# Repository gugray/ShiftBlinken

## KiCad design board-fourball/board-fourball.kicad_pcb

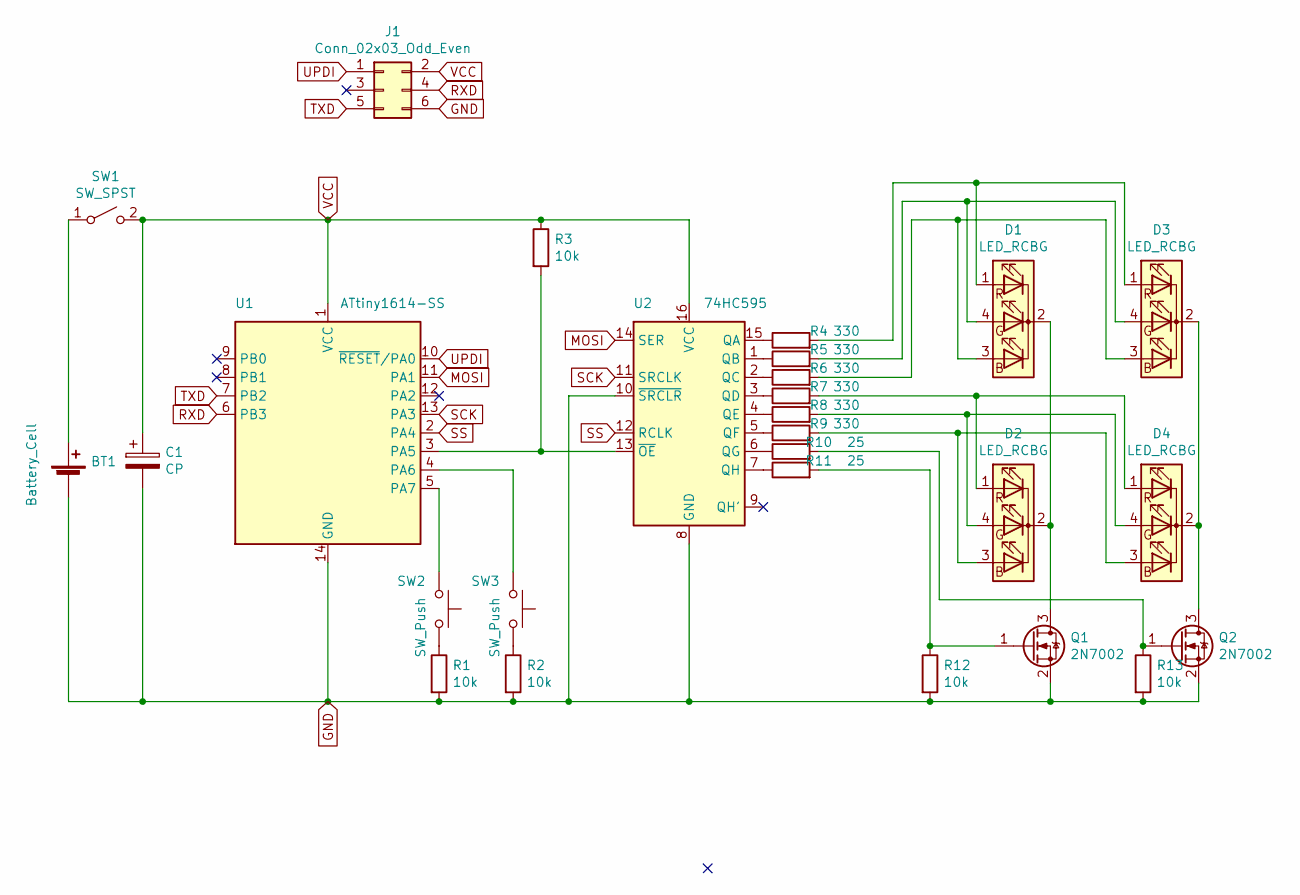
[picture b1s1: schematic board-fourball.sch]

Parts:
BT1: Battery_Cell; BatteryHolder_Keystone_3002_1x2032
C1: CP; CP_Radial_D5.0mm_P2.00mm
D1, D2, D3, D4: LED_RCBG; LED_D5.0mm-4_RGB
J1: Conn_02x03_Odd_Even; PinHeader_2x03_P2.54mm_Vertical
Q1, Q2: 2N7002; SOT-23
R1, R2, R3, R12, R13: 10k; R_0805_2012Metric
R4, R5, R6, R7, R8, R9: 330; R_0805_2012Metric
R10, R11: 25; R_0805_2012Metric
SW1: SW_SPST; SW_DPDT_CK_JS202011JCQN
SW2, SW3: SW_Push; SW_SPST_B3U-1000P
U1: ATtiny1614-SS; SOIC-14_3.9x8.7mm_P1.27mm
U2: 74HC595; SO-16_3.9x9.9mm_P1.27mm

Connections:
GND: BT1.2 (-), C1.2, J1.6, Q1.2 (S), Q2.2 (S), R1.2, R2.2, R12.2, R13.2, U1.14 (GND), U2.8 (GND), U2.10 (~SRCLR)
MOSI: U1.11 (PA1), U2.14 (SER)
unnamed: BT1.1 (+), SW1.1 (A)
unnamed: D1.1 (RA), D3.1 (RA), R4.2
unnamed: D1.2 (K), D2.2 (K), Q1.3 (D)
unnamed: D1.3 (BA), D3.3 (BA), R6.2
unnamed: D1.4 (GA), D3.4 (GA), R5.2
unnamed: D2.1 (RA), D4.1 (RA), R7.2
unnamed: D2.3 (BA), D4.3 (BA), R9.2
unnamed: D2.4 (GA), D4.4 (GA), R8.2
unnamed: D3.2 (K), D4.2 (K), Q2.3 (D)
unnamed: Q1.1 (G), R11.2, R12.1
unnamed: Q2.1 (G), R10.2, R13.1
unnamed: R1.1, SW2.2
unnamed: R2.1, SW3.2
unnamed: R3.2, U1.3 (PA5), U2.13 (~OE)
unnamed: R4.1, U2.15 (QA)
unnamed: R5.1, U2.1 (QB)
unnamed: R6.1, U2.2 (QC)
unnamed: R7.1, U2.3 (QD)
unnamed: R8.1, U2.4 (QE)
unnamed: R9.1, U2.5 (QF)
unnamed: R10.1, U2.6 (QG)
unnamed: R11.1, U2.7 (QH)
unnamed: SW2.1, U1.5 (PA7)
unnamed: SW3.1, U1.4 (PA6)
RXD: J1.4, U1.6 (PB3)
SCK: U1.13 (PA3), U2.11 (SRCLK)
SS: U1.2 (PA4), U2.12 (RCLK)
TXD: J1.5, U1.7 (PB2)
UPDI: J1.1, U1.10 (~RESET~/PA0)
VCC: C1.1, J1.2, R3.1, SW1.2 (B), U1.1 (VCC), U2.16 (VCC)

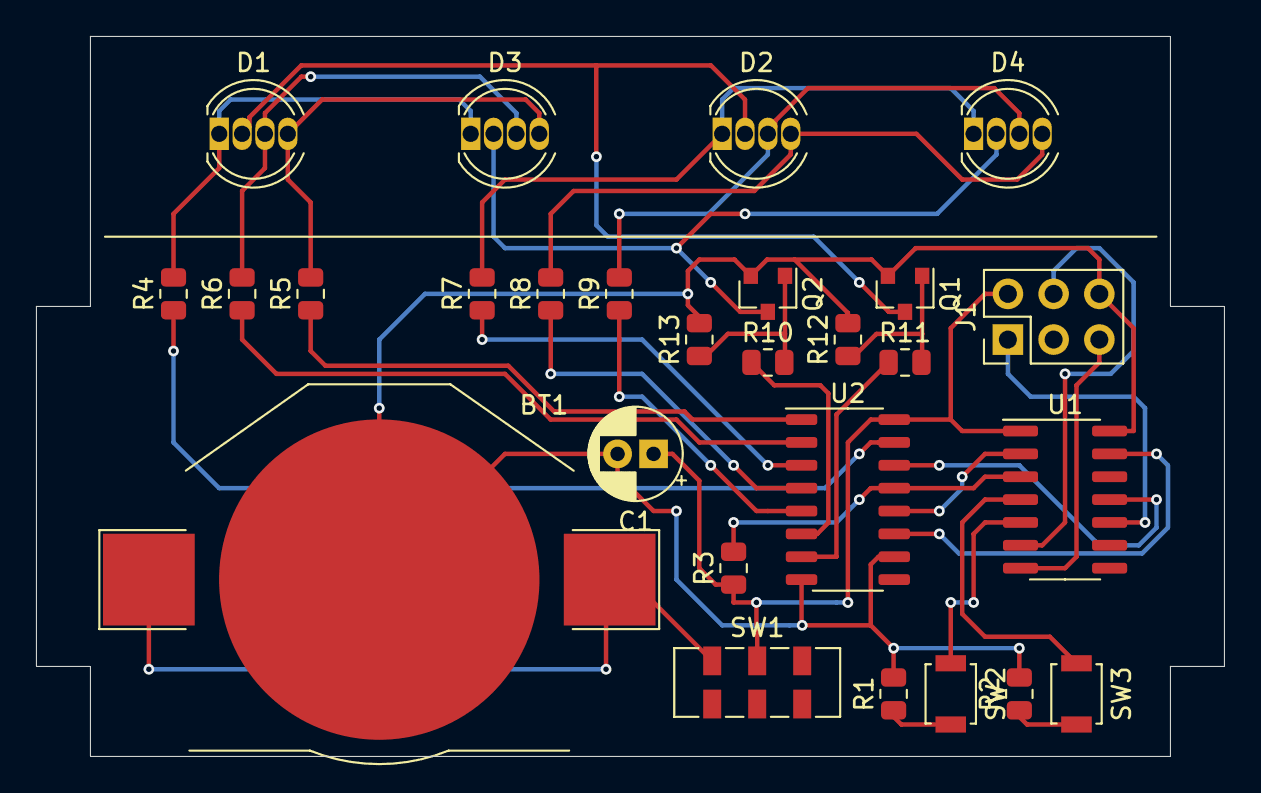
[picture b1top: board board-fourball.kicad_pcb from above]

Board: 2 copper layers, 66.0 x 40.0 mm, 27 parts (0 on the bottom side), 32 nets.

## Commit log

2023-06-16 initial commit / drives shift register with SPI
2023-06-17 2x2 RGB LEDs driven
